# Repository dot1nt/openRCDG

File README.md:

# openRCDG
An Arduino based rc drift gyro.

## Building
The easiest way to build and upload this project is to use the [platformio vscode extension](https://platformio.org/install/ide?install=vscode).

If you are building for a board other than the arduino micro, you will need to change/add the board in the platformio.ini file.

## Configuration
Configuration variables can be found in the config.h file.

## Hardware
I only tested this on an Arduino micro and nano, but it should work on most other boards as well.

Example schematic for an Arduino pro micro with GY-521 imu:

## PCB
Files for the pcb and case can be found in the pcb/case folders. The board works, but component placement/routing isn't optimal. The pcb uses components from a **3.3V** arduino pro micro and mpu6050 board. 3D printing the case works fine.

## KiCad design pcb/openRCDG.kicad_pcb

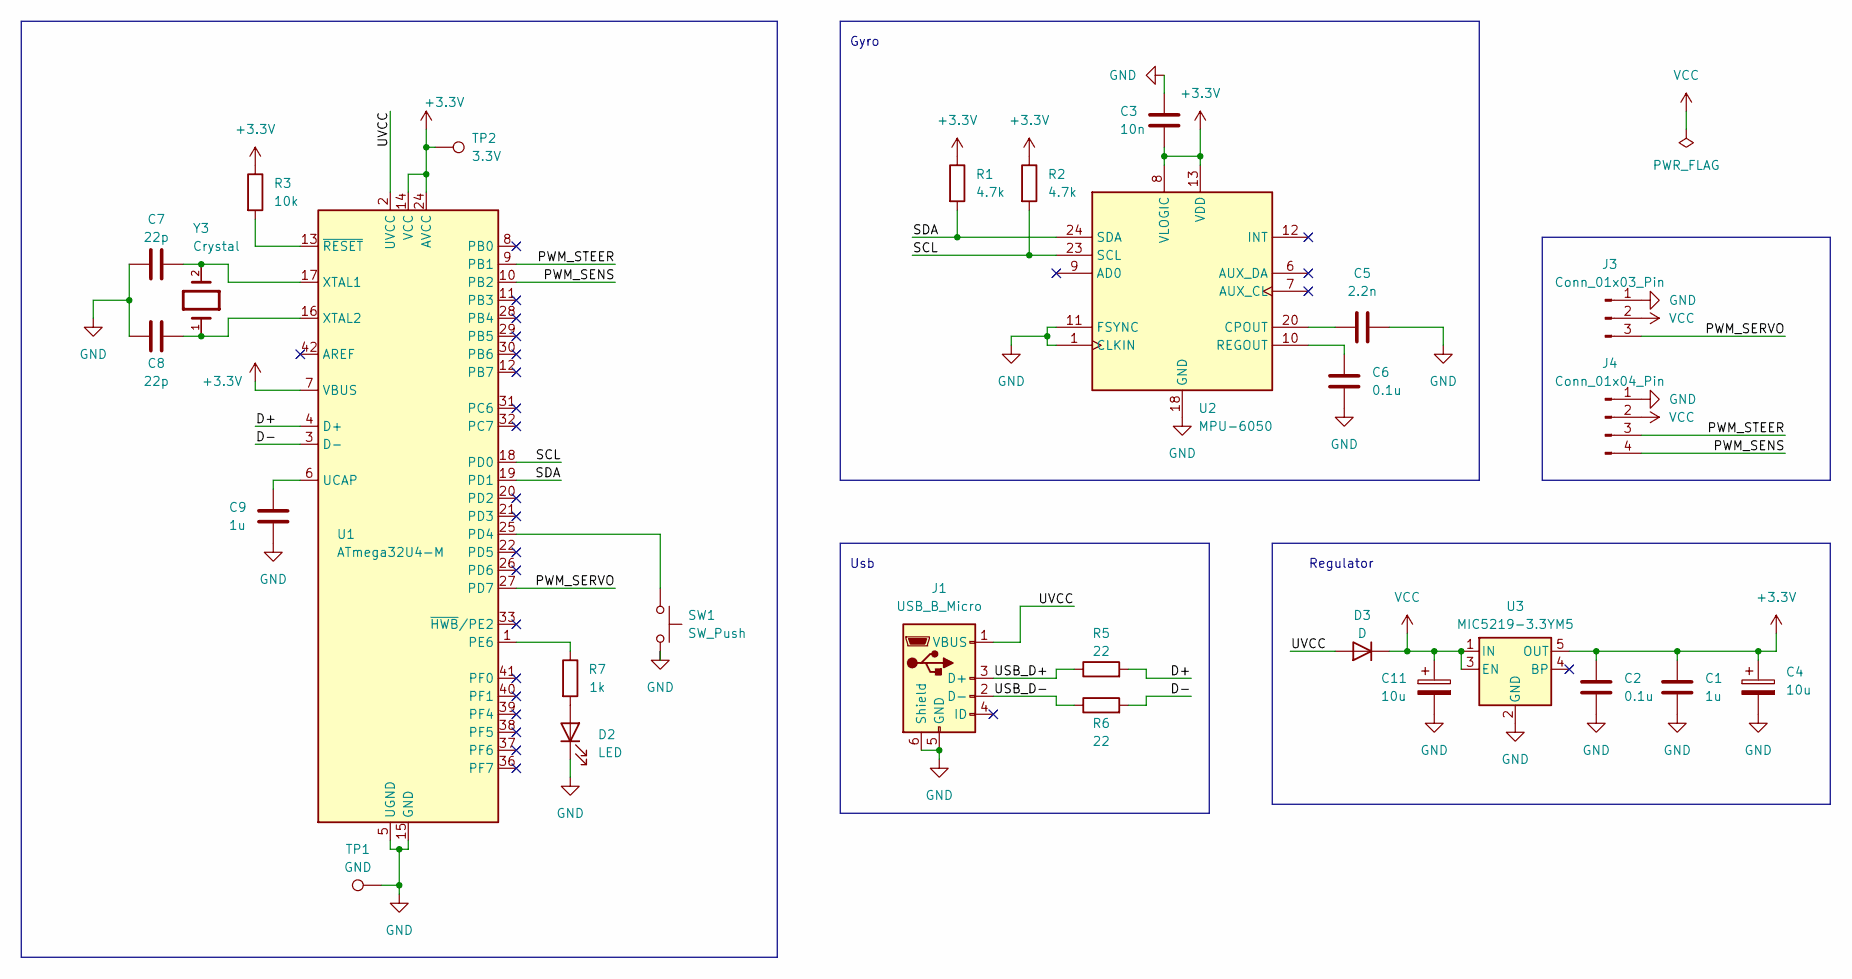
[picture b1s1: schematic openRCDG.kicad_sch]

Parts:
C1, C9: 1u; C_0402_1005Metric_Pad0.74x0.62mm_HandSolder
C2, C6: 0.1u; C_0402_1005Metric_Pad0.74x0.62mm_HandSolder
C3: 10n; C_0402_1005Metric_Pad0.74x0.62mm_HandSolder
C4, C11: 10u; CP_EIA-3216-18_Kemet-A_Pad1.58x1.35mm_HandSolder
C5: 2.2n; C_0402_1005Metric_Pad0.74x0.62mm_HandSolder
C7, C8: 22p; C_0402_1005Metric_Pad0.74x0.62mm_HandSolder
D2: LED; LED_0402_1005Metric_Pad0.77x0.64mm_HandSolder
D3: D; D_SOD-123
J1: USB_B_Micro; USB_Micro-B_Amphenol_10118194_Horizontal
J3: Conn_01x03_Pin; PinHeader_1x03_P1.00mm_Vertical
J4: Conn_01x04_Pin; PinHeader_1x04_P1.00mm_Vertical
R1, R2: 4.7k; R_0402_1005Metric_Pad0.72x0.64mm_HandSolder
R3: 10k; R_0402_1005Metric_Pad0.72x0.64mm_HandSolder
R5, R6: 22; R_0402_1005Metric_Pad0.72x0.64mm_HandSolder
R7: 1k; R_0402_1005Metric_Pad0.72x0.64mm_HandSolder
SW1: SW_Push; SW_Push_1P1T_NO_Vertical_Wuerth_434133025816
TP1: GND; TestPoint_Pad_D1.5mm
TP2: 3.3V; TestPoint_Pad_D1.5mm
U1: ATmega32U4-M; QFN-44-1EP_7x7mm_P0.5mm_EP5.2x5.2mm
U2: MPU-6050; InvenSense_QFN-24_4x4mm_P0.5mm
U3: MIC5219-3.3YM5; SOT-23-5
Y3: Crystal; arduino_micro_crystal

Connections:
+3.3V: C1.1, C2.1, C3.1, C4.1, R1.1, R2.1, R3.1, TP2.1, U1.7 (VBUS), U1.14 (VCC), U1.24 (AVCC), U1.34 (VCC), U1.44 (AVCC), U2.8 (VLOGIC), U2.13 (VDD), U3.5 (OUT)
/D+: R5.2, U1.4 (D+)
/D-: R6.2, U1.3 (D-)
/PWM_SENS: J4.4, U1.10 (PB2)
/PWM_SERVO: J3.3, U1.27 (PD7)
/PWM_STEER: J4.3, U1.9 (PB1)
/SCL: R2.2, U1.18 (PD0), U2.23 (SCL)
/SDA: R1.2, U1.19 (PD1), U2.24 (SDA)
/USB_D+: J1.3 (D+), R5.1
/USB_D-: J1.2 (D-), R6.1
/UVCC: D3.2 (A), J1.1 (VBUS), U1.2 (UVCC)
GND: C1.2, C2.2, C3.2, C4.2, C5.2, C6.2, C7.1, C8.1, C9.2, C11.2, D2.1 (K), J1.5 (GND), J1.6 (Shield), J3.1, J4.1, SW1.2, TP1.1, U1.5 (UGND), U1.15 (GND), U1.23 (GND), U1.35 (GND), U1.43 (GND), U1.45 (GND), U2.1 (CLKIN), U2.11 (FSYNC), U2.18 (GND), U3.2 (GND)
unnamed: D2.2 (A), R7.2
unnamed: SW1.1, U1.25 (PD4)
unnamed: R7.1, U1.1 (PE6)
unnamed: C9.1, U1.6 (UCAP)
unnamed: C7.2, U1.17 (XTAL1), Y3.2
unnamed: C8.2, U1.16 (XTAL2), Y3.1
unnamed: R3.2, U1.13 (~RESET)
unnamed: C5.1, U2.20 (CPOUT)
unnamed: C6.1, U2.10 (REGOUT)
VCC: C11.1, D3.1 (K), J3.2, J4.2, U3.1 (IN), U3.3 (EN)

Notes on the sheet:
Regulator
Usb
Gyro

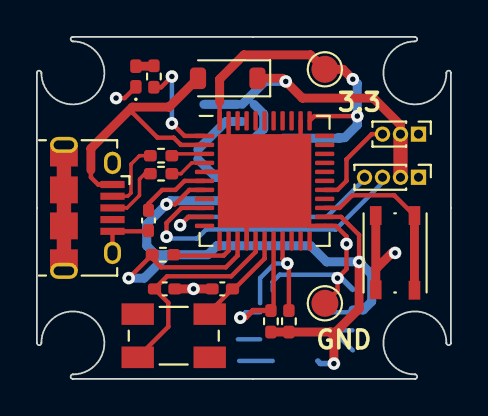
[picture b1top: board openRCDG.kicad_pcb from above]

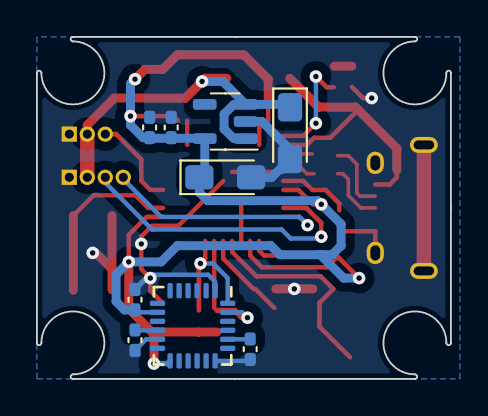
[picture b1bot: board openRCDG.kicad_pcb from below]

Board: 2 copper layers, 23.0 x 19.0 mm, 28 parts (9 on the bottom side), 22 nets.

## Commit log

2024-11-30 code and case improvements
